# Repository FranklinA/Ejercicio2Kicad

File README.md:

# Ejercicio2Kicad
Cuatro capas con Kicad

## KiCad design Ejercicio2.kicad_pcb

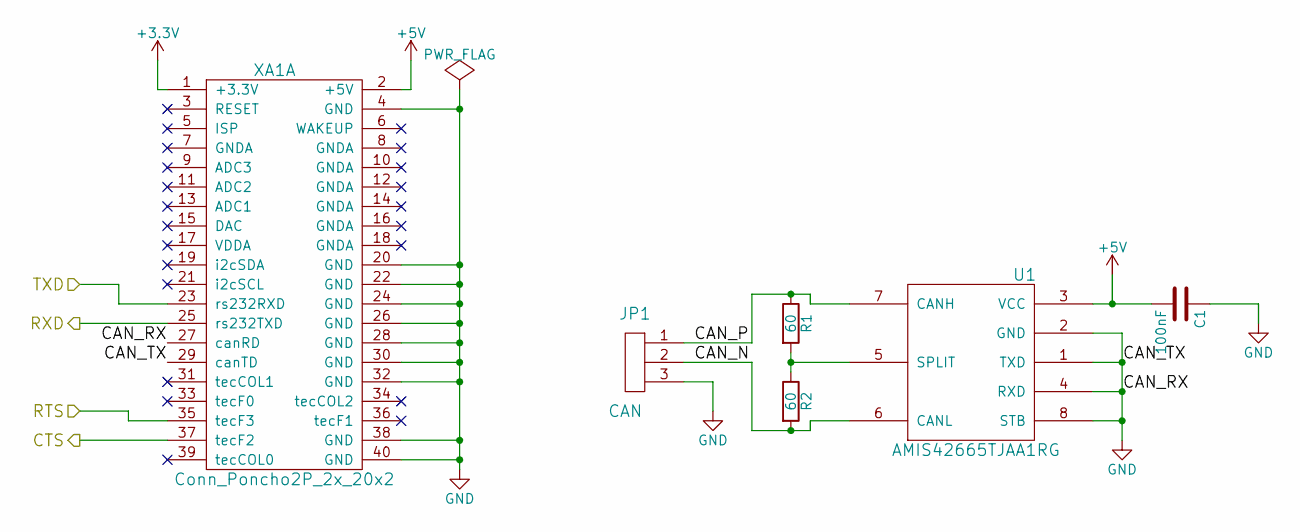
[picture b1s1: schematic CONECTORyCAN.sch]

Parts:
C1: 100nF; C_0603_HandSoldering; Digikey#: 311-1179-1-ND
JP1: CAN; CON_PALETA_3; Digikey#: A19470-ND
R1, R2: 60; R_1206_HandSoldering; Digikey#: Y149660R0000A0R-ND
U1: AMIS42665TJAA1RG; SOIC-8; Digikey#: 766-1006-1-ND
XA1: Conn_Poncho2P_2x_20x2; Conn_Poncho_Derecha; Digikey#: 952-1387-ND

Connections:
+3V3: XA1.1 (+3.3V); also elsewhere on the board
+5V: C1.2, U1.3 (VCC), XA1.2 (+5V)
/CON1: XA1.23 (rs232RXD); also elsewhere on the board
/CON2: XA1.25 (rs232TXD); also elsewhere on the board
/CON3: XA1.37 (tecF2); also elsewhere on the board
/CON4: XA1.35 (tecF3); also elsewhere on the board
/CONECTORyCAN/CAN_N: JP1.2, R2.2, U1.6 (CANL)
/CONECTORyCAN/CAN_P: JP1.1, R1.1, U1.7 (CANH)
GND: C1.1, JP1.3, U1.1 (TXD), U1.2 (GND), U1.4 (RXD), U1.8 (STB), XA1.4 (GND), XA1.20 (GND), XA1.22 (GND), XA1.24 (GND), XA1.26 (GND), XA1.27 (canRD), XA1.28 (GND), XA1.29 (canTD), XA1.30 (GND), XA1.32 (GND), XA1.38 (GND), XA1.40 (GND); also elsewhere on the board
unnamed: R1.2, R2.1, U1.5 (SPLIT)

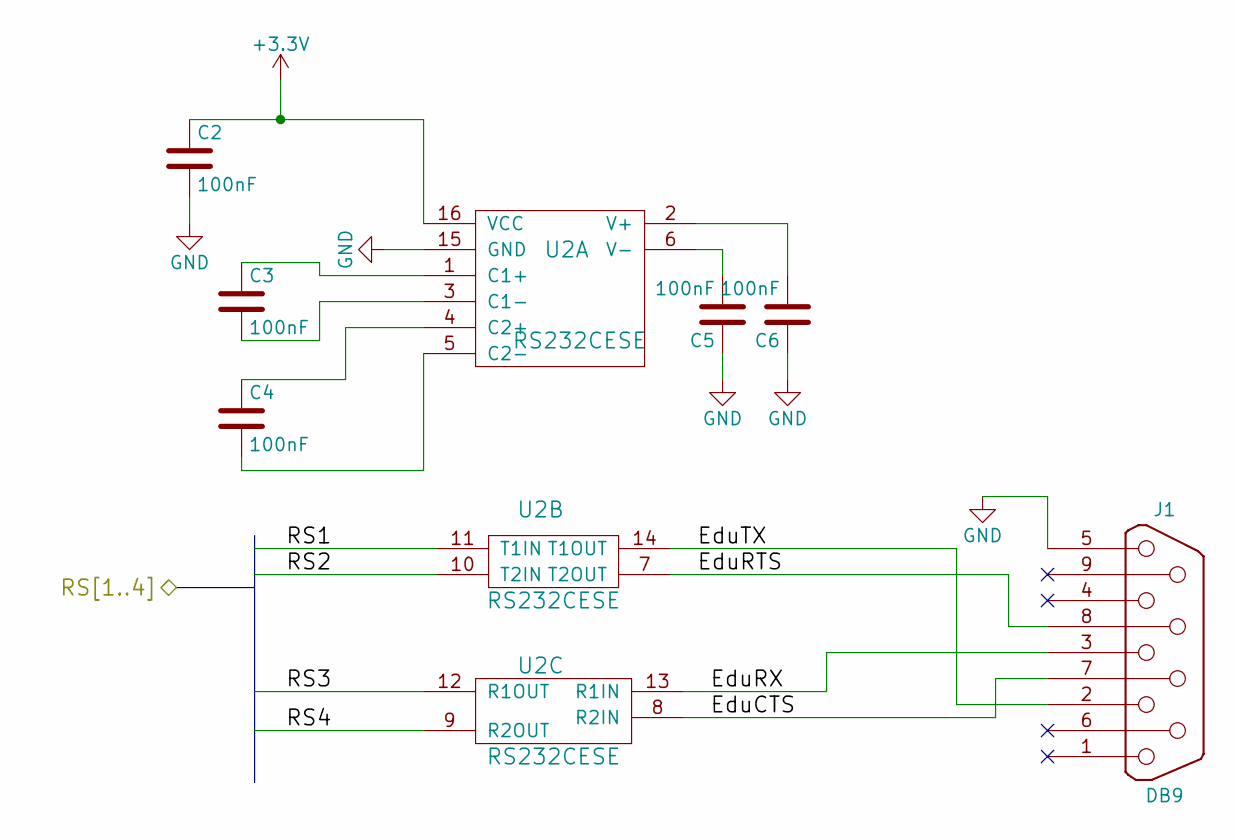
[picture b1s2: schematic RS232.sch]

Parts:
C2, C3, C4, C5, C6: 100nF; C_0603_HandSoldering; Digikey#: 311-1179-1-ND
J1: DB9; DB9_F_TH; Digikey#: S9554-ND
U2: RS232CESE; SP3232ECN-SOIC16N

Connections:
+3V3: C2.1, U2.16 (VCC); also elsewhere on the board
/CON1: U2.11 (T1IN); also elsewhere on the board
/CON2: U2.10 (T2IN); also elsewhere on the board
/CON3: U2.12 (R1OUT); also elsewhere on the board
/CON4: U2.9 (R2OUT); also elsewhere on the board
/RS232/EduCTS: J1.7, U2.8 (R2IN)
/RS232/EduRTS: J1.8, U2.7 (T2OUT)
/RS232/EduRX: J1.3, U2.13 (R1IN)
/RS232/EduTX: J1.2, U2.14 (T1OUT)
GND: C2.2, C5.1, C6.1, J1.5, U2.15 (GND); also elsewhere on the board
unnamed: C3.1, U2.1 (C1+)
unnamed: C3.2, U2.3 (C1-)
unnamed: C4.1, U2.4 (C2+)
unnamed: C4.2, U2.5 (C2-)
unnamed: C5.2, U2.6 (V-)
unnamed: C6.2, U2.2 (V+)

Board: 4 copper layers, 14 parts (0 on the bottom side), 20 nets, no tracks yet.

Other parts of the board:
XA?: Plantilla_Poncho_Derecha

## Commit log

2017-05-25 Practica 4 Capas kicad
    Desarrollo de esquemático y PCB para producción.
2017-05-25 Creación Readme
    ...
2017-05-25 Incluyendo imagen en el repositorio
    Incluyendo imagen con :
    ![GitHub Logo](/Kicad-Escuela-CESE.jpg)
2017-05-31 Actualizaciones ejercicio 29 de mayo 2017
    Definición de las Capas para 3V, 5V y GND.
